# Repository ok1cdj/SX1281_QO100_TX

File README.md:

# SX1281_QO100_TX
QO-100 SAT CW and Feld Hell Transmitter with OLED Display using 2.4 GHz LoRa module with TCXO by OM2JU and OK1CDJ

https://www.nicerf.com/products/detail/500mw-2-4ghz-lora-wireless-transceiver-module-lora1280f27-lora1281f27.html

Modes: CW and Feld Hell (122.5 Bd, decoded e.g. by fldigi). Feld Hell is sent as a beacon or as any text from the
[pyCWdclient](pyCWdclient/README.md) client or over HTTP - see [Feld Hell](#feld-hell).

*Maximal power output is 450mW. It is enought to work over satellite with 60cm DISH, but tested also with 35cm and helix feed.*

## Features
- Paddle input -IAMBIC keyer
- Straight key input
- Change frequency, power, keyer speed by rotary encoder
- Frequency callibration
- CW beacon mode
- cwdaemon compatible UDP server on port 6789
- WiFi client or AP mode
- Web interface for WiFi config
- Web interafce for tuning, change speed and power
- New: PTT output on ESP32 module pin-12. This is logic signal, one must add external NPN/MOSFET. Configurable delay.
- Wi-Fi keep-alive: modem sleep off, automatic reconnect (fixes drop-outs with mesh APs such as TP-Link Deco)
- Firmware and web files update over Wi-Fi (OTA) - see below
- Feld Hell: beacon set from the web page, text sent from the client or over HTTP - see below
- Python client [pyCWdclient](pyCWdclient/README.md) for desktop and iPad: CW and Feld Hell TX, Feld Hell RX,
  frequency and power control, QSO logging to Wavelog
- Web interface usable on mobile phones

## Python client (pyCWdclient)
[`pyCWdclient/`](pyCWdclient/README.md) is a desktop (Tk) and iPad (Pythonista) client for the keyer:
CW macros over UDP (cwdaemon protocol), Feld Hell TX through the web API, Feld Hell receiver
(Linux, audio from an SDR), TX frequency and power control, frequency memories and QSO logging
to Wavelog.

```sh
cd pyCWdclient
cp config.example.json config.json   # keyer IP, call, Wavelog
python3 pyCWdclient.py
```

## Used libraries
Adafruit GFX Library

Adafruit_SSD1306

SX12XX Library - https://github.com/StuartsProjects/SX12XX-LoRa

ESPAsyncWebServer - https://github.com/me-no-dev/ESPAsyncWebServer

AsyncTCP - https://github.com/me-no-dev/AsyncTCP

## Building with PlatformIO
`platformio.ini` builds with Arduino-ESP32 core 2.0.17 (core 3.x is not supported). The web
interface lives in `data/` and goes to the SPIFFS partition.

```sh
pio run -t upload        # firmware over USB
pio run -t uploadfs      # web files over USB
```

## OTA update
Open `http://<keyer IP>/update?apikey=<APIKEY>`, choose *Firmware* (`firmware.bin`) or
*Web files* (`spiffs.bin`) and press Update. The keyer restarts after a successful upload;
settings are kept. With PlatformIO:

```sh
KEYER_APIKEY=1111 pio run -e ota -t upload   --upload-port <keyer IP>
KEYER_APIKEY=1111 pio run -e ota -t uploadfs --upload-port <keyer IP>
```

There is no automatic rollback - a firmware that does not start needs a USB flash
(hold BOOT, press EN).

## Feld Hell
Standard Feld Hell (7x14 font, 245 pixels/s, 2.5 characters/s, on/off keying), decoded by the
Feld Hell mode of fldigi. Text, number of repetitions (0 = until Stop) and pause between them
are set on the web page and kept after restart; `%CALL%` in the text is replaced by MyCall.
Start/Stop from the web page, from the menu (*Beacon FHELL*) or by HTTP:

```sh
curl "http://<keyer IP>/hell?apikey=<APIKEY>&cmd=start"   # cmd=stop, no cmd = status
```

Any text can be sent once with `cmd=send&txt=<text>`; text sent while the keyer is still
transmitting is appended (up to 512 characters). This is what the pyCWdclient client uses in its
Hell mode (macros and free text); the client also receives Feld Hell from an SDR.

Break (web, UDP) or the encoder push button stops Feld Hell and drops the rest of the text.
CW text is not sent while Feld Hell is being transmitted.

## User interface

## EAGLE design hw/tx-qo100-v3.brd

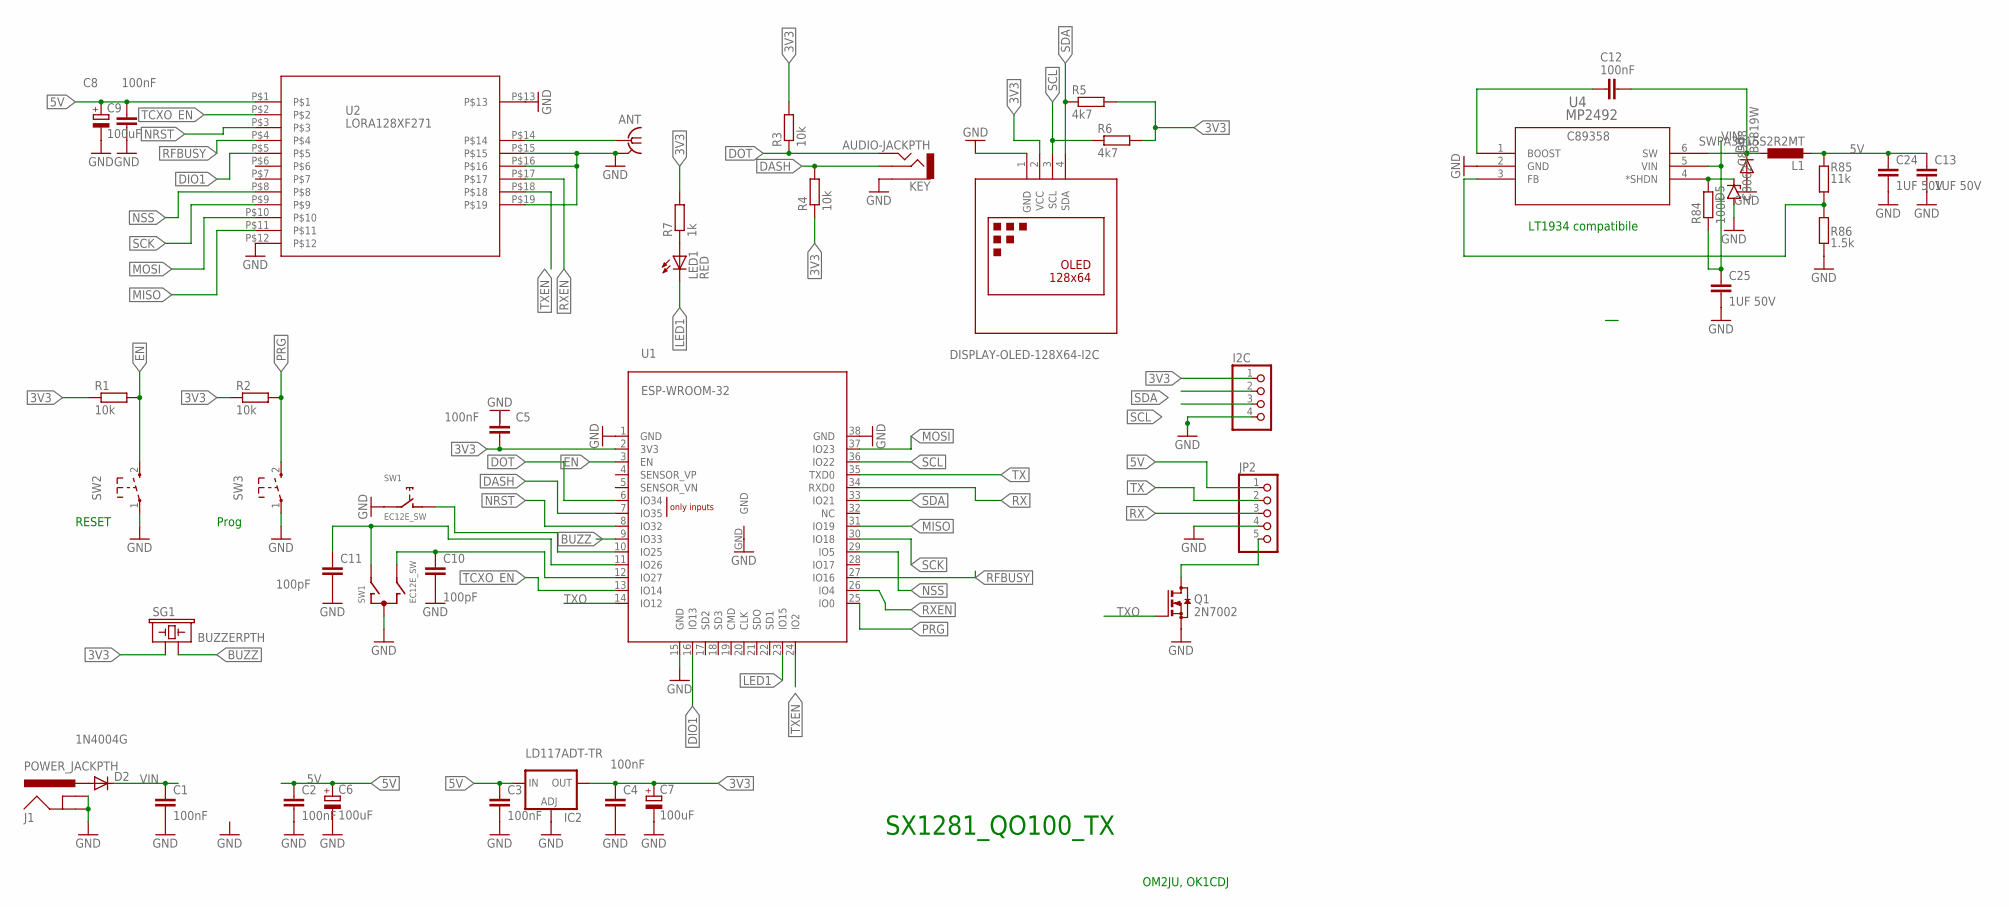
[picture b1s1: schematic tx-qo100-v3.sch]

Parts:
ANT: SMA-142-0711-821/826; J502-ND-142-0711-821/826
C1, C2, C3, C4, C5, C8, C12: 100nF; C0603
C6, C7, C9: 100uF; SMC_B; LCSC_PART C16133
C10, C11: 100pF; C0603
C13, C24, C25: 1UF 50V; C0603; LCSC_PART C15849
D2: 1N4004G; DO-214AC; LCSC_PART C433394
D5: C8062; SOD80C; LCSC_PART C8062
D6: B5819W; SOD123; LCSC_PART C8598
I2C: PINHD-1X4; 1X04
IC2: LD117ADT-TR; DPACK; LCSC_PART C358375
J1: POWER_JACKPTH; POWER_JACK_PTH
JP2: PINHD-1X5/90; 1X05/90
KEY: AUDIO-JACKPTH; AUDIO-JACK
L1: SWPA3015S2R2MT; L2825P; LCSC_PART C43389
LED1: RED; CHIP-LED0805; LCSC_PART C84256
Q1: 2N7002; SOT23; LCSC_PART C8545
R1, R2, R3, R4: 10k; R0603
R5, R6: 4k7; R0603
R7: 1k; R0603
R84: 100k; R0603
R85: 11k; R0603
R86: 1.5k; R0603
SG1: BUZZERPTH; BUZZER-12MM; LCSC_PART C360607
SW1: EC12E_SW; ALPS_EC12E_SW
SW2, SW3: SW_TACT_2P-3X6; SW_TACT_3X6; LCSC_PART C520860
U1: ESP-WROOM-32
U2: LORA128XF271; LORA128XF27
U4: MP2492; SOT-6_S; LCSC_PART C89358
U$1: DISPLAY-OLED-128X64-I2C

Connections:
3V3: C4.1, C5.1, C7.+, I2C.1, IC2.4 (OUT), R1.1, R2.1, R3.2, R4.1, R5.2, R6.2, R7.2, SG1.+ (1), U1.2 (3V3), U$1.2 (VCC)
5V: C2.1, C3.1, C6.+, C8.1, C9.+, C13.1, C24.1, IC2.3 (IN), JP2.1, L1.2, R85.1, U2.P$1
BST: C12.2, U4.1 (BOOST)
BUZZ: SG1.- (2), U1.9 (IO33)
DASH: KEY.2, R4.2, U1.7 (IO35)
DIO1: U1.16 (IO13), U2.P$5
DOT: KEY.5, R3.1, U1.6 (IO34)
EN: R1.2, SW2.2 (3), U1.3 (EN)
GND: ANT.G@1 (2), ANT.G@2 (2), ANT.G@3 (2), ANT.G@4 (2), C1.2, C2.2, C3.2, C4.2, C5.2, C6.-, C7.-, C8.2, C9.-, C10.2, C11.2, C13.2, C24.2, C25.2, D5.A, D6.A, I2C.4, IC2.1 (ADJ), J1.GND, J1.GNDBREAK, JP2.4, KEY.1, Q1.2 (S), R86.1, SW1.C, SW1.E (2), SW2.1, SW3.1, U1.1 (GND), U1.15 (GND), U1.38 (GND), U1.GND, U2.P$12, U2.P$13, U2.P$15, U2.P$16, U2.P$19, U4.2 (GND), U$1.1 (GND)
IN: D2.A, J1.PWR
LED1: LED1.C, U1.23 (IO15)
MISO: U1.31 (IO19), U2.P$11
MOSI: U1.37 (IO23), U2.P$10
unnamed: ANT.1, U2.P$14
unnamed: C10.1, SW1.B, U1.12 (IO27)
unnamed: LED1.A, R7.1
unnamed: C11.1, SW1.A, U1.11 (IO26)
unnamed: SW1.D (1), U1.10 (IO25)
unnamed: JP2.5, Q1.3 (D)
unnamed: D5.C, R84.2, U4.4 (*SHDN)
unnamed: R85.2, R86.2, U4.3 (FB)
NRST: U1.8 (IO32), U2.P$3
NSS: U1.29 (IO5), U2.P$8
PRG: R2.2, SW3.2 (3), U1.25 (IO0)
RFBUSY: U1.27 (IO16), U2.P$4
RX: JP2.3, U1.34 (RXD0)
RXEN: U1.26 (IO4), U2.P$17
SCK: U1.30 (IO18), U2.P$9
SCL: I2C.3, R6.1, U1.36 (IO22), U$1.3 (SCL)
SDA: I2C.2, R5.1, U1.33 (IO21), U$1.4 (SDA)
SW: C12.1, D6.C, L1.1, U4.6 (SW)
TCXO_EN: U1.13 (IO14), U2.P$2
TX: JP2.2, U1.35 (TXD0)
TXEN: U1.24 (IO2), U2.P$18
TXO: Q1.1 (G), U1.14 (IO12)
VIN: C1.1, C25.1, D2.C, R84.1, U4.5 (VIN)

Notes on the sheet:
RESET
Prog
SX1281_QO100_TX
OM2JU, OK1CDJ
LT1934 compatibile

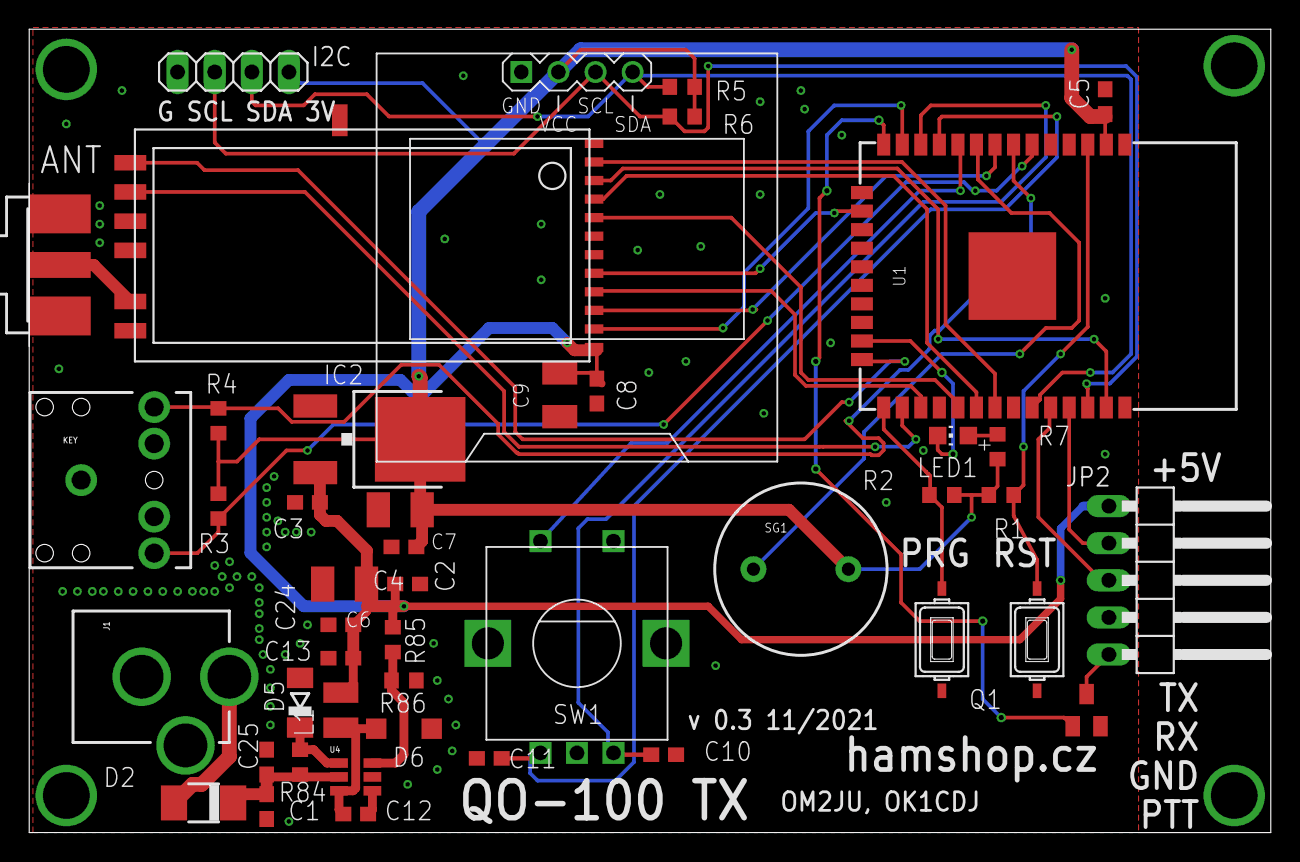
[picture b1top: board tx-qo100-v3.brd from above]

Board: 2 copper layers, 85.0 x 55.0 mm, 45 parts (0 on the bottom side), 36 nets.

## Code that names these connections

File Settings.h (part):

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#define MOSI 23                                 //MOSI on SPI3 

#define NRESET 32                               //reset pin on LoRa device
#define RFBUSY 16                               //busy line

#define LED1 15                                 //on board LED, high for on
#define DIO1 13                                 //DIO1 pin on LoRa device, used for RX and TX done 
#define DIO2 -1                                 //DIO2 pin on LoRa device, normally not used so set to -1 
#define DIO3 -1                                 //DIO3 pin on LoRa device, normally not used so set to -1
#define RX_EN 4                                //pin for RX enable, used on some SX128X devices, set to -1 if not used
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#define BUZZER 33                               //pin for buzzer, set to -1 if not used 
#define VCCPOWER 17    //JU-not needed by module          //pin controls power to external devices
#define LORA_DEVICE DEVICE_SX1281               //we need to define the device we are using
#define TCXO_EN 14
#define PTT_OUT 12

#define LOOP_PTT_MULT_VALUE 1000  // Value by which PttTimeout counter is multiplied - we need this since mail loop is running very fast
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
#define ROTARY_ENC_PUSH  25    // Rotary encoder pushbutton
//
#define KEYER_DOT       34    // Morse keyer DOT          NOTE: GPIOs 34 to 39 INPUTs only / No internal pullup / No int. pulldown
#define KEYER_DASH      35    // Morse keyer DASH

//

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
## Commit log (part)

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2021-08-24 Schematic
2021-09-04 Update SX1281_QO100_TX.ino
    TX is now working, user can now set TX power from 50mW to 450mW, parameters such as Callsign, WiFi SSID, Password can be configured and are stored in NVM
2021-09-09 Update SX1281_QO100_TX.ino
    JU:
    - Buzzer-frequency made configurable and stored in NV memory
    - added timeout for display items other than main screen
    - minor changes in graphic layout
2021-09-13 Web interface
2021-09-13 WIFI config and web interface
2021-09-16 Upadate of web interface
    added frequency and power control
2021-09-16 Update SX1281_QO100_TX.ino
    - UDP Keying and wpm speed setting functional
    - Timeout on menu items functional
2021-09-21 HW update
2021-09-24 Added LED to PIN 15
2021-10-23 Update index.html
    - Now FRQ_INDEX is exchanged with C program and frequency value is calculated from this index.
    - Calculation of the frequency had to be moved into periodic routine since changes in the input element are registered only at from submit
    - Upon change of WPM or PWR the form is submitted automatically
    - Minor cosmetic changes
2021-10-23 Update bootstrap.min.css
    Background color changed to silver
2021-10-23 Update SX1281_QO100_TX.ino
    Changes in HTTP request interaction part
2021-10-26 User interface image
2021-10-26 Frequency change on background
    Better look of user intreface and frequency change on backround.
2021-11-03 Implementation of Feld Hell beacon
    firt test of Feld Hell mode
2021-11-08 Update SX1281_QO100_TX.ino
    - Morse message concept changed to use Queues, should be safer
    - UDP: now can receive some invalid Morse characters; these are encoded by character value >= 128
    - UDP: remote part can adjust Frequency, Power and WPM by special UDP packet
2021-11-08 Update Settings.h
    - Added Morse_Coding_table2[] - non-morse character encoding up to length 6
2021-11-08 Update index.html
    - added sending dots button
2021-12-08 Update SX1281_QO100_TX.ino
    Changes OM2JU:
    - added decoding of optional 2nd UPD packet with repeated information (if first UPD is missed the second will be used = improves reliability over WiFi)
    - code cleanup around interrupt routine + general cleanup
2022-04-03 Update SX1281_QO100_TX.ino
    OM2JU
    - added PTT output. The PTT delay is configurable from menu and stored as parameter in flash
    - code cleanup
2022-04-03 Update Settings.h
    OM2JU
    - added PTT output. The PTT delay is configurable from menu and stored as parameter in flash
    - the LOOP_PTT_MULT_VALUE value is set to 1000 in order to give cca milisecond resolution when multiplied by PttTimeout value
2022-04-28 Update SX1281_QO100_TX.ino
    wrong channel initialization
2022-07-26 Update SX1281_QO100_TX.ino
    JU 2022-07-26:
    - Updated edge detection in Rotary encoder ISR onTimer() so that it now works reliably
    - WPM setting via UDP - resulting WPM is made a bit slower so that there are less "pauses" when keying via UDP
    - see Calc_WPM_dot_delay_a_bit_slower()
2022-07-26 Update Settings.h
    JU 2022-07-26:
    v1.1 - corrected edge processing from rotary encoder
2023-02-02 Update Settings.h
    Program_Version "v1.3" // 2023-02-02 JU, Added support for Iambic-B keying. Based on request of Markus DL6YYM
2023-02-02 Update SX1281_QO100_TX.ino
    Program_Version "v1.3" // 2023-02-02 JU, Added support for Iambic-B keying. Based on request of Markus DL6YYM
2023-02-10 v1.5
2025-05-19 Eagle and Gerbers

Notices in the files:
Settings.h:
Programs for Arduino - Copyright of the author Stuart Robinson - 02/03/20
parts and their libraries:
diy-modules: Released under the Creative Commons Attribution 4.0 International License: http://creativecommons.org/licenses/by/4.0
